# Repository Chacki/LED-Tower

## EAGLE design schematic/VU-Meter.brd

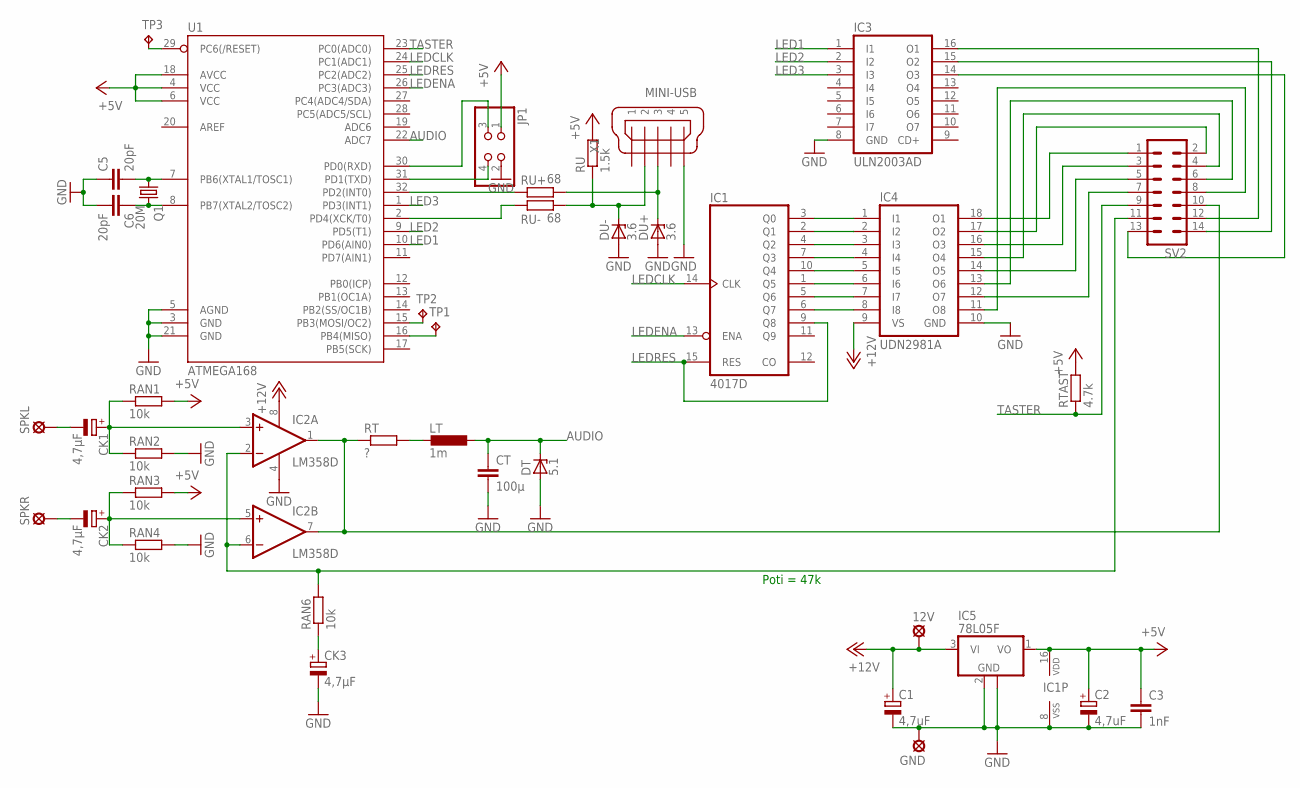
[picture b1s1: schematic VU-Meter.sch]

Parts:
12V: LSP13
C1, C2: 4,7uF; 153CLV-0405
C3: 1nF; C0805K
C5, C6: 20pF; C0805K
CK1, CK2, CK3: 4,7µF; 153CLV-0405
CT: 100µ; C1210K
DT: 5.1; SOD80C
DU+: 3.6; SOD80C
DU-: 3.6; SOD80C
GND: LSP13
IC1: 4017D; SO16
IC2: LM358D; SO08
IC3: ULN2003AD; SO16
IC4: UDN2981A; DIL18
IC5: 78L05F; SOT89
JP1: PINHD-2X2/90; 2X02/90
LT: 1m; PIS2816
Q1: 20M; SM49
RAN1, RAN2, RAN3, RAN4, RAN6: 10k; R0603
RT: ?; R0603
RTAST: 4.7k; R0603
RU: 1.5k; R0603
RU+: 68; R0603
RU-: 68; R0603
SPKL: LSP13
SPKR: LSP13
SV2: ML14
TP1, TP2, TP3: TPB1,27; B1,27
U1: ATMEGA168; TQFP32-08
X1: MINI-USB; 32005-400

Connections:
+5V: C2.+, C3.1, IC1.16 (VDD), IC5.1 (VO), JP1.1, RAN1.2, RAN3.2, RTAST.2, RU.2, U1.4 (VCC), U1.6 (VCC), U1.18 (AVCC)
+12V: 12V.MP, C1.+, IC2.8 (V+), IC4.9 (VS), IC5.3 (VI)
AUDIO: CT.1, DT.C, LT.1, U1.22 (ADC7)
GND: C1.-, C2.-, C3.2, C5.1, C6.2, CK3.-, CT.2, DT.A, DU+.A, DU-.A, GND.MP, IC1.8 (VSS), IC2.4 (V-), IC3.8 (GND), IC4.10 (GND), IC5.2 (GND), IC5.2@1 (GND), JP1.2, RAN2.2, RAN4.2, U1.3 (GND), U1.5 (AGND), U1.21 (GND), X1.5
LED1: IC3.1 (I1), U1.10 (PD6(AIN0))
LED2: IC3.2 (I2), U1.9 (PD5(T1))
LED3: IC3.3 (I3), U1.1 (PD3(INT1))
LEDCLK: IC1.14 (CLK), U1.24 (PC1(ADC1))
LEDENA: IC1.13 (ENA), U1.26 (PC3(ADC3))
LEDRES: IC1.9 (Q8), IC1.15 (RES), U1.25 (PC2(ADC2))
unnamed: C6.1, Q1.2, U1.8 (PB7(XTAL2/TOSC2))
unnamed: C5.2, Q1.1, U1.7 (PB6(XTAL1/TOSC1))
unnamed: TP1.TP, U1.16 (PB4(MISO))
unnamed: IC1.3 (Q0), IC4.1 (I1)
unnamed: IC1.2 (Q1), IC4.2 (I2)
unnamed: IC1.4 (Q2), IC4.3 (I3)
unnamed: IC1.7 (Q3), IC4.4 (I4)
unnamed: IC1.10 (Q4), IC4.5 (I5)
unnamed: IC1.1 (Q5), IC4.6 (I6)
unnamed: IC1.5 (Q6), IC4.7 (I7)
unnamed: IC1.6 (Q7), IC4.8 (I8)
unnamed: TP2.TP, U1.15 (PB3(MOSI/OC2))
unnamed: JP1.3, U1.30 (PD0(RXD))
unnamed: TP3.TP, U1.29 (PC6(/RESET))
unnamed: LT.2, RT.2
unnamed: CK1.+, IC2.3 (+IN), RAN1.1, RAN2.1
unnamed: IC2.1 (OUT), IC2.7 (OUT), RT.1, SV2.10
unnamed: IC4.18 (O1), SV2.1
unnamed: IC4.17 (O2), SV2.2
unnamed: IC4.16 (O3), SV2.3
unnamed: IC4.15 (O4), SV2.4
unnamed: IC4.14 (O5), SV2.5
unnamed: IC4.13 (O6), SV2.6
unnamed: IC4.12 (O7), SV2.7
unnamed: IC4.11 (O8), SV2.8
unnamed: IC3.14 (O3), SV2.13
unnamed: IC3.15 (O2), SV2.14
unnamed: IC3.16 (O1), SV2.12
unnamed: JP1.4, U1.31 (PD1(TXD))
unnamed: CK2.+, IC2.5 (+IN), RAN3.1, RAN4.1
unnamed: CK1.-, SPKL.MP
unnamed: CK2.-, SPKR.MP
unnamed: IC2.2 (-IN), IC2.6 (-IN), RAN6.2, SV2.11
unnamed: CK3.+, RAN6.1
unnamed: RU+.1, U1.32 (PD2(INT0))
unnamed: RU-.1, U1.2 (PD4(XCK/T0))
unnamed: DU+.C, RU+.2, X1.3
unnamed: DU-.C, RU.1, RU-.2, X1.2
TASTER: RTAST.1, SV2.9, U1.23 (PC0(ADC0))

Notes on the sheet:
Poti = 47k

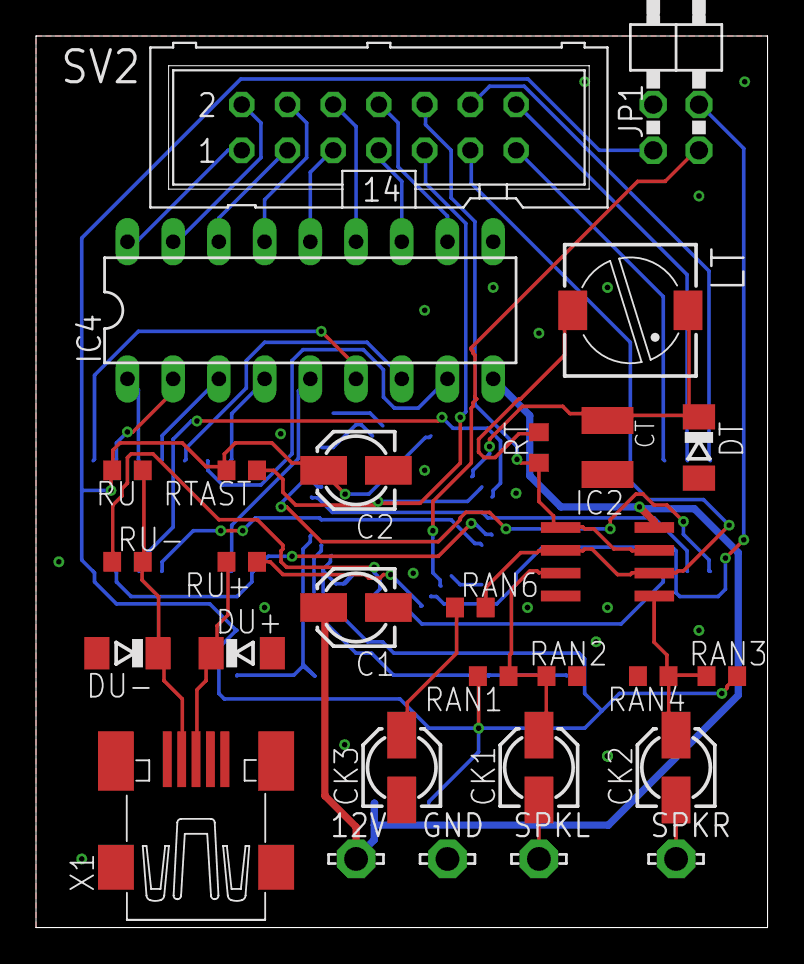
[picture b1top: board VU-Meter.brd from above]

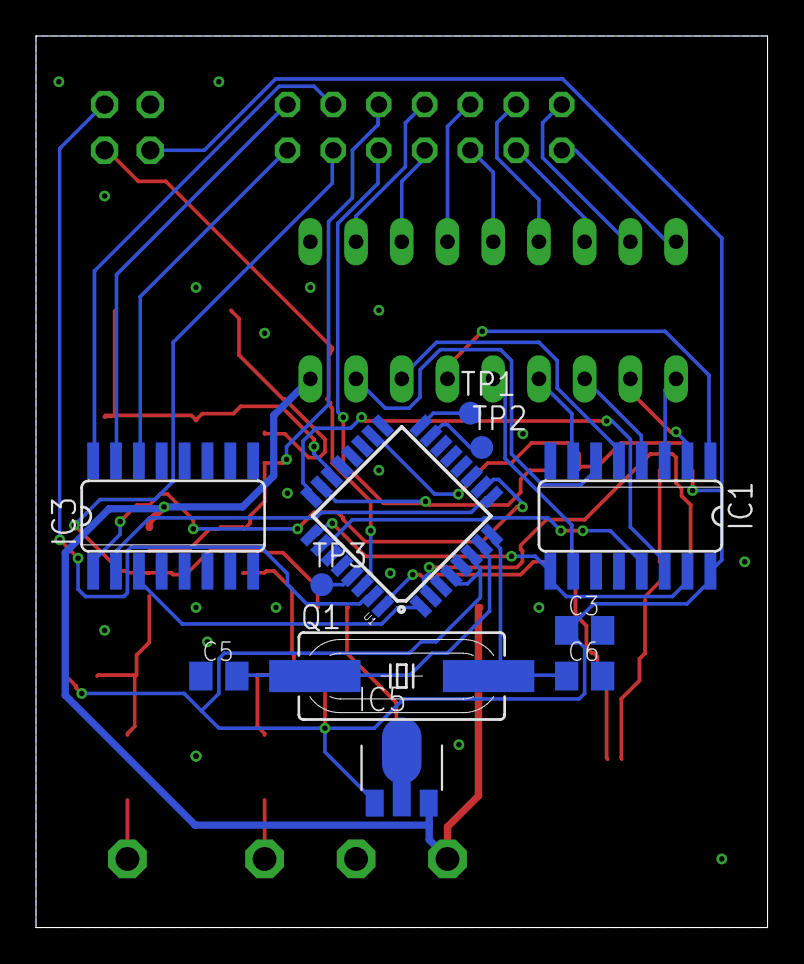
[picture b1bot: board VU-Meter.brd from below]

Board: 2 copper layers, 40.6 x 49.5 mm, 40 parts (11 on the bottom side), 49 nets.

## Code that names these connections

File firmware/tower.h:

#include <stdint.h>
#ifndef TOWER_H
#define TOWER_H
#ifndef F_CPU
#define F_CPU 20000000
#endif
#define TASTER PC0
#define LEDCLK PC1
#define LEDRES PC2
#define LEDENA PC3
void initTower(void);
uint32_t getTime();
void setColor(int i, int red, int green, int blue);
#endif

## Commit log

2018-04-08 Added schematic
2018-04-08 Added firmware

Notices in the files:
parts and their libraries:
SparkFun-DigitalIC: Licensing: Creative Commons ShareAlike 4.0 International - https://creativecommons.org/licenses/by-sa/4.0
